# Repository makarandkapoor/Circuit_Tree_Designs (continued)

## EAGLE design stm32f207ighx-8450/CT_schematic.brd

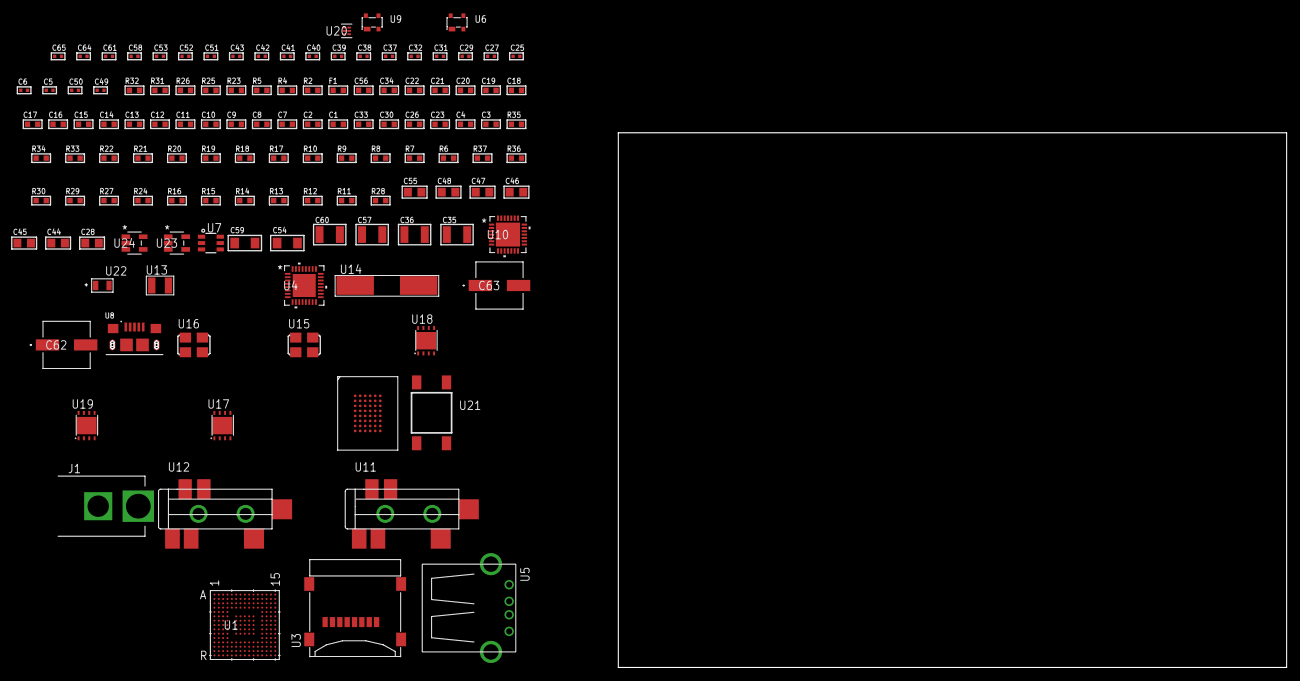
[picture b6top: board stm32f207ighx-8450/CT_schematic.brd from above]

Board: 2 copper layers, 125 parts (0 on the bottom side), 71 nets, no tracks yet.

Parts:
C1: 1e-08; C0603
C2, C7, C56: 1e-06; C0603
C3, C4, C26, C30, C33: 2.2e-06; C0603
C5, C6: 1e-11; C0402
C8, C9, C10, C11, C12, C13, C14, C15, C16, C17, C18, C19, C20, C21, C22: 1e-07; C0603
C23: 4.7e-06; C0603
C25, C27, C29, C31, C32, C39, C40, C41, C42, C43, C61: 1e-07; C0402
C28, C44, C45, C46, C47, C48, C55: 1e-05; C0805
C34: 0.0001; R0603
C35, C36: 2.2e-05; C1210
C37, C38: 1e-09; C0402
C49, C50: 2.2e-11; C0402
C51, C52, C53, C58, C64, C65: 1e-08; C0402
C54, C59: 1e-05; C1206
C57, C60: 1e-05; C1210
C62, C63: 0.0001; EXV-9H
F1: 240.0; L0603
J1: PJ-037B; PJ-037B_PACKAGE
R2, R26, R32: 1000.0; R0603
R4, R5: 4700.0; R0603
R6, R7, R8, R9, R10, R18, R19, R33, R34: 10000.0; R0603
R11, R12, R13, R14, R15, R16, R24, R27, R29, R30: 100000.0; R0603
R17, R20, R21, R22: 47000.0; R0603
R23: 680.0; R0603
R25: 806.0; R0603
R28: 153694.38; R0603
R31: 3900.0; R0603
R35: 82000.0; R0603
R36: 300000.0; R0603
R37: 120000.0; R0603
U1: STM32f207IGH6; UFBGA176_25
U2: IS61WV102416BLL-10MLI
U3: 0472192001; MOLEX_47219-2001
U4: TUSB1210BRHBR; RHB32_3P45X3P45
U5: 61400416021; USB-A-H
U6, U9: prtr5v0u2ax; SOT143B
U7: MAX4995AAUT+T; SOT-23-6
U8: 10118193-0001LF; FCI_10118193-0001LF
U10: WM8731CLSEFL; QFN-28
U11, U12: SJ-43515TS-SMT-TR
U13: ABS07-32.768KHZ-7-T
U14: ABLS-12.288MHZ-B4-T
U15: ASFL1-19.2MHZ-NCS; ASFL1
U16: ASFL1-25MHZ-NCS; ASFL1
U17, U19: LP3878SDX-ADJ/NOPB; WSON-8
U18: LP2951ACSDX/NOPB; WSON-8
U20: TPS3895ADRYR; SON-6
U21: 4-1437565-2; SW_4-1437565-2
U22: Q65110A2395; LGM67K-G1J2-24-Z
U23, U24: nc7sz125m5x; NC7SZ125M5X

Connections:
CLK_CRYSTAL_U1_E1: C5.1, U1.E1, U13.1
CLK_CRYSTAL_U1_F1: C6.1, U1.F1, U13.2
CLK_CRYSTAL_U10_1: C49.1, U10.1, U14.1
CLK_CRYSTAL_U10_2: C50.1, U10.2, U14.2
CLK_U1_G1: U1.G1, U16.3
CLK_U4_1: U4.1, U15.3
GND: C1.2, C2.2, C3.2, C4.2, C5.2, C6.2, C7.2, C8.2, C9.2, C10.2, C11.2, C12.2, C13.2, C14.2, C15.2, C16.2, C17.2, C18.2, C19.2, C20.2, C21.2, C22.2, C23.2, C25.2, C26.2, C27.2, C28.2, C29.2, C30.2, C31.2, C32.2, C33.2, C34.2, C38.2, C39.2, C40.2, C41.2, C42.2, C43.2, C44.2, C45.2, C46.2, C47.2, C48.2, C49.2, C50.2, C51.2, C52.2, C53.2, C54.2, C55.2, C56.2, C57.2, C58.2, C59.2, C60.2, C61.2, C62.2, C63.2, C64.2, C65.2, J1.2, R2.2, R6.2, R7.2, R17.2, R19.2, R20.2, R21.2, R22.2, R26.2, R29.2, R32.2, R35.2, R37.2, U1.D5, U1.D7, U1.D8, U1.D9, U1.F2, U1.F6, U1.F7, U1.F8, U1.F9, U1.F10, U1.F12, U1.G2, U1.G6, U1.G7, U1.G8, U1.G9, U1.G10, U1.G12, U1.H6, U1.H7, U1.H8, U1.H9, U1.H10, U1.H12, U1.J6, U1.J7, U1.J8, U1.J9, U1.J10, U1.K6, U1.K7, U1.K8, U1.K9, U1.K10, U1.M1, U1.M8, U1.M9, U1.N1, U2.D1, U2.E6, U3.6, U3.G1, U3.G2, U3.G3, U3.G4, U4.23, U4.33, U5.4, U5.5, U5.6, U6.1, U7.2, U8.5, U8.6, U8.7, U8.8, U8.9, U9.1, U10.4, U10.15, U10.19, U10.25, U10.26, U10.29, U11.1, U12.1, U15.2, U16.2, U17.3, U17.PAD, U18.3, U18.4, U18.PAD, U19.3, U19.PAD, U20.2, U22.C, U23.1, U23.3, U24.1, U24.3
NET_U1_D6: R6.1, U1.D6
NET_U1_F13: C4.1, U1.F13
NET_U1_J1: R4.1, U1.J1, U23.4
NET_U1_L4: R7.1, U1.L4
NET_U1_M10: C3.1, U1.M10
NET_U1_R1: C1.1, C2.1, F1.1, U1.P1, U1.R1
NET_U1_R15: U21.3, U21.4
NET_U2_A2: R9.1, U2.A2
NET_U2_B5: R8.1, U2.B5
NET_U2_G5: R10.1, U2.G5
NET_U4_11: R18.1, U4.11
NET_U4_12: C33.1, U4.12
NET_U4_14: R19.1, U4.14
NET_U4_20: C30.1, U4.20
NET_U4_27: R5.1, U4.27, U24.4
NET_U5_1: C34.1, U4.22, U5.1, U6.4, U7.1
NET_U5_2: U4.19, U5.2, U6.3
NET_U5_3: U4.18, U5.3, U6.2
NET_U7_3: R17.1, U7.3
NET_U7_4: U4.17, U7.4
NET_U10_20: C43.1, C48.1, U10.20
NET_U11_2: C36.1, R21.1, U11.2
NET_U11_5: C35.1, R20.1, U11.5
NET_U12_5: C37.1, C38.1, R22.1, R23.1, U12.5
NET_U17_1: C53.1, U17.1
NET_U17_6: R25.2, R26.1, U17.6
NET_U17_8: R24.1, U17.8
NET_U18_5: R27.1, U18.5
NET_U18_7: R28.2, R29.1, U18.7
NET_U19_1: C58.1, U19.1
NET_U19_6: R31.2, R32.1, U19.6
NET_U19_8: R30.1, U19.8
NET_U20_1: R34.1, R35.1, U20.1
NET_U20_3: R36.2, R37.1, U20.3
NET_U20_4: R33.1, U20.4, U23.2, U24.2
NET_U21_1: R2.1, U21.1, U21.2
PROC_I2S2_SCK: U1.D14, U10.7
PROC_I2S2_SD: U1.C13, U10.8
PROC_I2S2_WS: U1.B4, U10.9, U10.11
PROC_SDIO_CK: R12.1, U1.A12, U3.5
PROC_SDIO_CMD: R11.1, U1.D12, U3.3
PROC_SDIO_D0: R13.1, U1.G14, U3.7
PROC_SDIO_D1: R14.1, U1.F14, U3.8
PROC_SDIO_D2: R15.1, U1.B14, U3.1
PROC_SDIO_D3: R16.1, U1.B13, U3.2
PROC_USB_OTG_FS_DM: U8.2, U9.3
PROC_USB_OTG_FS_DP: U8.3, U9.2
PROC_USB_OTG_FS_VBUS: U8.1, U9.4
PROC_USB_OTG_HS_ULPI_CK: U1.P4, U4.26
PROC_USB_OTG_HS_ULPI_D0: U1.R2, U4.3
PROC_USB_OTG_HS_ULPI_D1: U1.R5, U4.4
PROC_USB_OTG_HS_ULPI_D2: U1.R4, U4.5
PROC_USB_OTG_HS_ULPI_D3: U1.R12, U4.6
PROC_USB_OTG_HS_ULPI_D4: U1.R13, U4.7
PROC_USB_OTG_HS_ULPI_D5: U1.P12, U4.9
PROC_USB_OTG_HS_ULPI_D6: U1.P13, U4.10
PROC_USB_OTG_HS_ULPI_D7: U1.A6, U4.13
PROC_USB_OTG_HS_ULPI_DIR: U1.E4, U4.31
PROC_USB_OTG_HS_ULPI_NXT: U1.H4, U4.2
PROC_USB_OTG_HS_ULPI_STP: U1.M2, U4.29
VCC_S1_8V6: C54.1, C56.1, C59.1, C62.1, C63.1, J1.1, R24.2, R30.2, U17.4, U18.8, U19.4
VCC_TIER1_1V8: C7.1, C8.1, C9.1, C10.1, C11.1, C12.1, C13.1, C14.1, C15.1, C16.1, C17.1, C18.1, C19.1, C20.1, C21.1, C22.1, C23.1, C27.1, C28.1, C31.1, C32.1, C39.1, C40.1, C41.1, C42.1, C44.1, C45.1, C46.1, C47.1, C55.1, C61.1, C64.1, C65.1, F1.2, R4.2, R5.2, R11.2, R12.2, R13.2, R14.2, R15.2, R16.2, R18.2, R25.1, R33.2, R34.2, R36.1, U1.C1, U1.C5, U1.C7, U1.C8, U1.C9, U1.F3, U1.G3, U1.G13, U1.H13, U1.J12, U1.J13, U1.K4, U1.N8, U1.N9, U1.N10, U3.4, U4.28, U4.30, U4.32, U10.3, U10.5, U10.12, U10.18, U17.5, U20.6, U23.5, U24.5
VCC_TIER1_3V3: C25.1, C26.1, C29.1, C51.1, C52.1, C57.1, R8.2, R9.2, R10.2, R27.2, R28.1, U2.D6, U2.E1, U4.21, U15.4, U16.4, U18.1
VCC_TIER1_5V0: C60.1, R31.1, U7.5, U19.5

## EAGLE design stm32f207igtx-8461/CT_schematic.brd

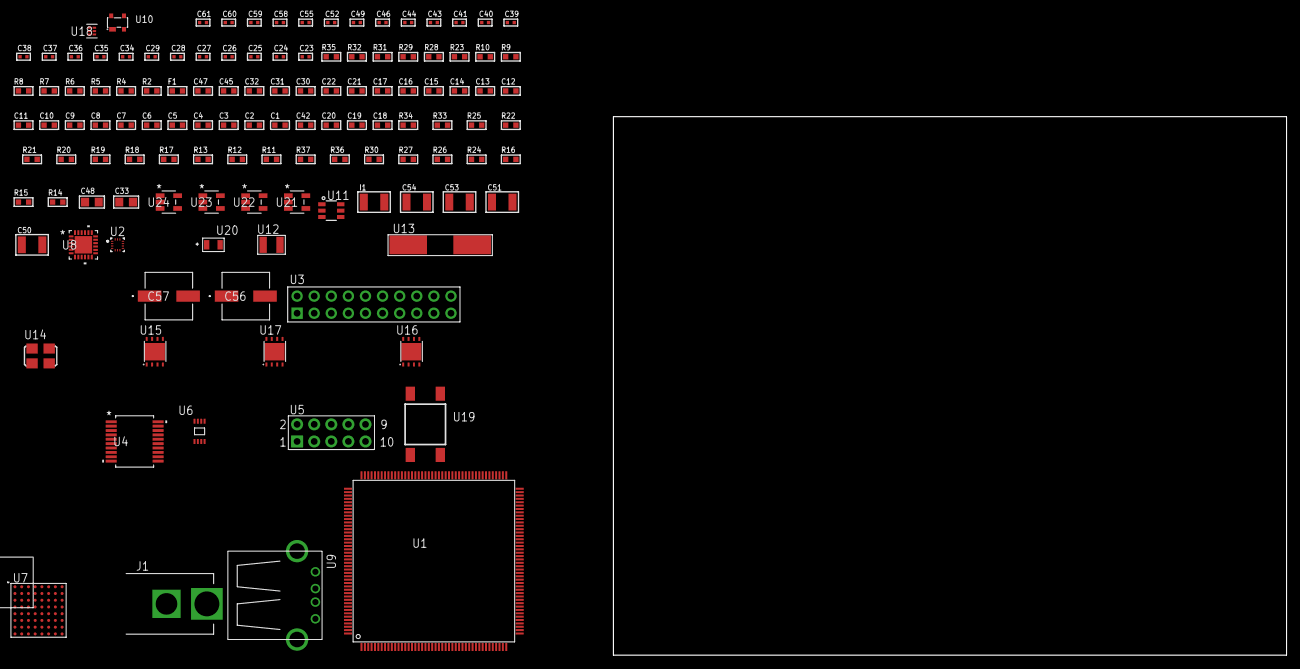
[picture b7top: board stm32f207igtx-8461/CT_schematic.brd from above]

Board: 2 copper layers, 100.0 x 80.0 mm, 123 parts (0 on the bottom side), 120 nets, no tracks yet.

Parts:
C1, C22, C30, C31, C32: 1e-06; C0603
C2, C3, C4, C5, C6, C7, C8, C9, C10, C11, C12, C13, C14, C15, C16, C17: 1e-07; C0603
C18: 4.7e-06; C0603
C19, C20, C42: 2.2e-06; C0603
C21: 1e-08; C0603
C23, C24, C25, C26: 1e-11; C0402
C27, C28, C29, C35, C37, C39, C55: 1e-07; C0402
C33: 4.7e-06; C0805
C34, C36, C38, C40, C41, C43, C44, C46, C49, C52, C58, C59, C60, C61: 1e-08; C0402
C45: 0.0001; R0603
C47: 8e-07; R0603
C48: 1e-05; C0805
C50, C51, C53, C54: 1e-05; C1210
C56, C57: 0.0001; EXV-9H
F1: 240.0; L0603
I1: 1.5e-05; L1210
J1: PJ-037B; PJ-037B_PACKAGE
R2, R29, R32: 1000.0; R0603
R4, R5, R6: 4700.0; R0603
R7, R8, R9, R10: 2200.0; R0603
R11, R12, R13, R17, R18, R19, R20, R21, R33, R34: 10000.0; R0603
R14, R15, R16, R24, R26, R27, R30: 100000.0; R0603
R22: 47000.0; R0603
R23: 8060.0; R0603
R25: 36000.0; R0603
R28: 2231.0; R0603
R31: 3900.0; R0603
R35: 9100.0; R0603
R36: 680000.0; R0603
R37: 120000.0; R0603
U1: STM32F207IGT6; LQFP176
U2: BMC150; LGA14R35P5X6_200X200X100
U3: TST-110-05-T-D-RA
U4: MAX3218EAP+T; SSOP-20
U5: HTSS-105-01-G-D
U6: 24AA00T-I/MNY; TDFN-8/6MM
U7: PC28F512P33BFD
U8: USB3317C-CP-TR; QFN-24
U9: 61400416021; USB-A-H
U10: prtr5v0u2ax; SOT143B
U11: MAX4995AAUT+T; SOT-23-6
U12: ABS07-32.768KHZ-7-T
U13: ABLS-25.000MHZ-B2F-T
U14: ASFL1-26MHZ-NCS; ASFL1
U15: LP2951ACSDX/NOPB; WSON-8
U16, U17: LP3878SDX-ADJ/NOPB; WSON-8
U18: TPS3895ADRYR; SON-6
U19: 4-1437565-2; SW_4-1437565-2
U20: Q65110A2395; LGM67K-G1J2-24-Z
U21, U22, U23, U24: nc7sz125m5x; NC7SZ125M5X

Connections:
CLK_CRYSTAL_U1_9: C23.1, U1.9, U12.1
CLK_CRYSTAL_U1_10: C24.1, U1.10, U12.2
CLK_CRYSTAL_U1_29: C25.1, U1.29, U13.1
CLK_CRYSTAL_U1_30: C26.1, U1.30, U13.2
CLK_U8_23: U8.23, U14.3
GND: C1.2, C2.2, C3.2, C4.2, C5.2, C6.2, C7.2, C8.2, C9.2, C10.2, C11.2, C12.2, C13.2, C14.2, C15.2, C16.2, C17.2, C18.2, C19.2, C20.2, C21.2, C22.2, C23.2, C24.2, C25.2, C26.2, C27.2, C28.2, C29.2, C30.2, C31.2, C32.2, C34.2, C35.2, C36.2, C37.2, C38.2, C39.2, C40.2, C41.2, C42.2, C43.2, C44.2, C45.2, C46.2, C47.2, C48.2, C49.2, C50.2, C51.2, C52.2, C53.2, C54.2, C55.2, C56.2, C57.2, C58.2, C59.2, C60.2, C61.2, J1.2, R2.2, R11.2, R22.2, R23.2, R26.2, R29.2, R32.2, R35.2, R37.2, U1.14, U1.22, U1.37, U1.48, U1.61, U1.71, U1.90, U1.102, U1.113, U1.126, U1.135, U1.148, U1.158, U2.1, U2.6, U2.7, U2.9, U3.4, U3.6, U3.8, U3.10, U3.12, U3.14, U3.16, U3.18, U3.20, U4.5, U4.17, U4.20, U5.9, U6.4, U7.B2, U7.H2, U7.H4, U7.H6, U8.1, U8.25, U9.4, U9.5, U9.6, U10.1, U11.2, U14.2, U15.3, U15.4, U15.PAD, U16.3, U16.PAD, U17.3, U17.PAD, U18.2, U20.C, U21.2, U21.3, U22.1, U22.3, U23.1, U23.3, U24.1, U24.3
NET_U1_31: R5.1, U1.31, U23.4
NET_U1_39: C21.1, C22.1, F1.1, U1.38, U1.39
NET_U1_45: R9.1, U1.45, U6.6
NET_U1_46: R10.1, U1.46, U6.5
NET_U1_81: C19.1, U1.81
NET_U1_125: C20.1, U1.125
NET_U1_164: R7.1, U1.164, U2.11
NET_U1_166: R11.1, U1.166
NET_U1_168: R8.1, U1.168, U2.14
NET_U1_176: U19.3, U19.4
NET_U4_1: I1.1, U4.1
NET_U4_2: R14.1, U4.2
NET_U4_3: R15.1, U4.3
NET_U4_4: R16.1, U4.4
NET_U4_15: C32.1, U4.15
NET_U4_16: C33.2, U4.16
NET_U4_18: C33.1, U4.18
NET_U4_19: C31.1, U4.19
NET_U5_3: U4.12, U5.3
NET_U5_4: U4.11, U5.4
NET_U5_5: U4.14, U5.5
NET_U5_6: U4.13, U5.6
NET_U7_A4: C39.1, C40.1, U7.A4
NET_U7_C6: R20.1, U7.C6
NET_U7_D4: R4.1, U7.D4, U22.4
NET_U8_4: C42.1, U8.4
NET_U8_22: R6.1, U8.22, U24.4
NET_U8_24: R23.1, U8.24
NET_U9_1: C45.1, U8.2, U9.1, U10.4, U11.1
NET_U9_2: U8.5, U9.2, U10.3
NET_U9_3: U8.6, U9.3, U10.2
NET_U11_3: R22.1, U11.3
NET_U11_4: U8.7, U11.4
NET_U15_5: R24.1, U15.5
NET_U15_7: R25.2, R26.1, U15.7
NET_U16_1: C49.1, U16.1
NET_U16_6: R28.2, R29.1, U16.6
NET_U16_8: R27.1, U16.8
NET_U17_1: C52.1, U17.1
NET_U17_6: R31.2, R32.1, U17.6
NET_U17_8: R30.1, U17.8
NET_U18_1: R34.1, R35.1, U18.1
NET_U18_3: R36.2, R37.1, U18.3
NET_U18_4: R33.1, U18.4, U21.4, U22.2, U23.2, U24.2
NET_U19_1: R2.1, U19.1, U19.2
PROC_FSMC_A0: U1.16, U7.A1
PROC_FSMC_A1: U1.17, U7.B1
PROC_FSMC_A2: U1.18, U7.C1
PROC_FSMC_A3: U1.19, U7.D1
PROC_FSMC_A4: U1.20, U7.D2
PROC_FSMC_A5: U1.21, U7.A2
PROC_FSMC_A6: U1.60, U7.C2
PROC_FSMC_A7: U1.63, U7.A3
PROC_FSMC_A8: U1.64, U7.B3
PROC_FSMC_A9: U1.65, U7.C3
PROC_FSMC_A10: U1.66, U7.D3
PROC_FSMC_A11: U1.67, U7.C4
PROC_FSMC_A12: U1.106, U7.A5
PROC_FSMC_A13: U1.107, U7.B5
PROC_FSMC_A14: U1.108, U7.C5
PROC_FSMC_A15: U1.109, U7.D7
PROC_FSMC_A16: U1.99, U7.D8
PROC_FSMC_A17: U1.100, U7.A7
PROC_FSMC_A18: U1.101, U7.B7
PROC_FSMC_A19: U1.2, U7.C7
PROC_FSMC_A20: U1.3, U7.C8
PROC_FSMC_A21: U1.4, U7.A8
PROC_FSMC_A22: U1.5, U7.G1
PROC_FSMC_A23: U1.1, U7.H8
PROC_FSMC_A24: U1.156, U7.B6
PROC_FSMC_CLK: U1.145, U7.E6
PROC_FSMC_D0: U1.104, U7.F2
PROC_FSMC_D1: U1.105, U7.E2
PROC_FSMC_D2: U1.142, U7.G3
PROC_FSMC_D3: U1.143, U7.E4
PROC_FSMC_D4: U1.68, U7.E5
PROC_FSMC_D5: U1.69, U7.G5
PROC_FSMC_D6: U1.70, U7.G6
PROC_FSMC_D7: U1.73, U7.H7
PROC_FSMC_D8: U1.74, U7.E1
PROC_FSMC_D9: U1.75, U7.E3
PROC_FSMC_D10: U1.76, U7.F3
PROC_FSMC_D11: U1.77, U7.F4
PROC_FSMC_D12: U1.78, U7.F5
PROC_FSMC_D13: U1.96, U7.H5
PROC_FSMC_D14: U1.97, U7.G7
PROC_FSMC_D15: U1.98, U7.E7
PROC_FSMC_NE4: R18.1, U1.155, U7.B4
PROC_FSMC_NL: R17.1, U1.165, U7.F6
PROC_FSMC_NOE: R19.1, U1.146, U7.F8
PROC_FSMC_NWAIT: U1.150, U7.F7
PROC_FSMC_NWE: R21.1, U1.147, U7.G8
PROC_SYS_JTCK_SWCLK: U1.137, U3.9
PROC_SYS_JTDO_SWO: U1.161, U3.13
PROC_SYS_JTMS_SWDIO: U1.124, U3.7
PROC_UART4_RX: U1.41, U4.9
PROC_UART4_TX: U1.40, U4.7
PROC_USB_OTG_HS_ULPI_CK: U1.51, U8.12
PROC_USB_OTG_HS_ULPI_D0: U1.47, U8.16
PROC_USB_OTG_HS_ULPI_D1: U1.56, U8.15
PROC_USB_OTG_HS_ULPI_D2: U1.57, U8.14
PROC_USB_OTG_HS_ULPI_D3: U1.79, U8.13
PROC_USB_OTG_HS_ULPI_D4: U1.80, U8.11
PROC_USB_OTG_HS_ULPI_D5: U1.92, U8.10
PROC_USB_OTG_HS_ULPI_D6: U1.93, U8.9
PROC_USB_OTG_HS_ULPI_D7: U1.163, U8.8
PROC_USB_OTG_HS_ULPI_DIR: U1.13, U8.19
PROC_USB_OTG_HS_ULPI_NXT: U1.35, U8.18
PROC_USB_OTG_HS_ULPI_STP: U1.32, U8.20
RST_OUT_U3_SRESET_B: R13.1, U3.15, U21.1
VCC_S1_13V0: C47.1, C50.1, C53.1, C56.1, C57.1, J1.1, R27.2, R30.2, U15.8, U16.4, U17.4
VCC_TIER1_1V8: C27.1, C44.1, C48.1, C58.1, C59.1, C60.1, C61.1, R24.2, R25.1, U2.8, U8.21, U15.1, U21.5, U22.5, U23.5, U24.5
VCC_TIER1_3V3: C1.1, C2.1, C3.1, C4.1, C5.1, C6.1, C7.1, C8.1, C9.1, C10.1, C11.1, C12.1, C13.1, C14.1, C15.1, C16.1, C17.1, C18.1, C28.1, C29.1, C30.1, C34.1, C35.1, C36.1, C37.1, C38.1, C41.1, C43.1, C46.1, C51.1, C55.1, F1.2, I1.2, R4.2, R5.2, R6.2, R7.2, R8.2, R9.2, R10.2, R12.1, R12.2, R13.2, R14.2, R15.2, R16.2, R17.2, R18.2, R19.2, R20.2, R21.2, R28.1, R33.2, R34.2, R36.1, U1.6, U1.15, U1.23, U1.36, U1.49, U1.62, U1.72, U1.82, U1.91, U1.103, U1.114, U1.127, U1.136, U1.149, U1.159, U1.172, U2.10, U2.12, U2.13, U3.1, U4.6, U6.8, U7.A6, U7.D5, U7.D6, U7.G4, U7.H3, U8.3, U8.17, U14.4, U16.5, U18.6
VCC_TIER1_5V0: C54.1, R31.1, U11.5, U17.5

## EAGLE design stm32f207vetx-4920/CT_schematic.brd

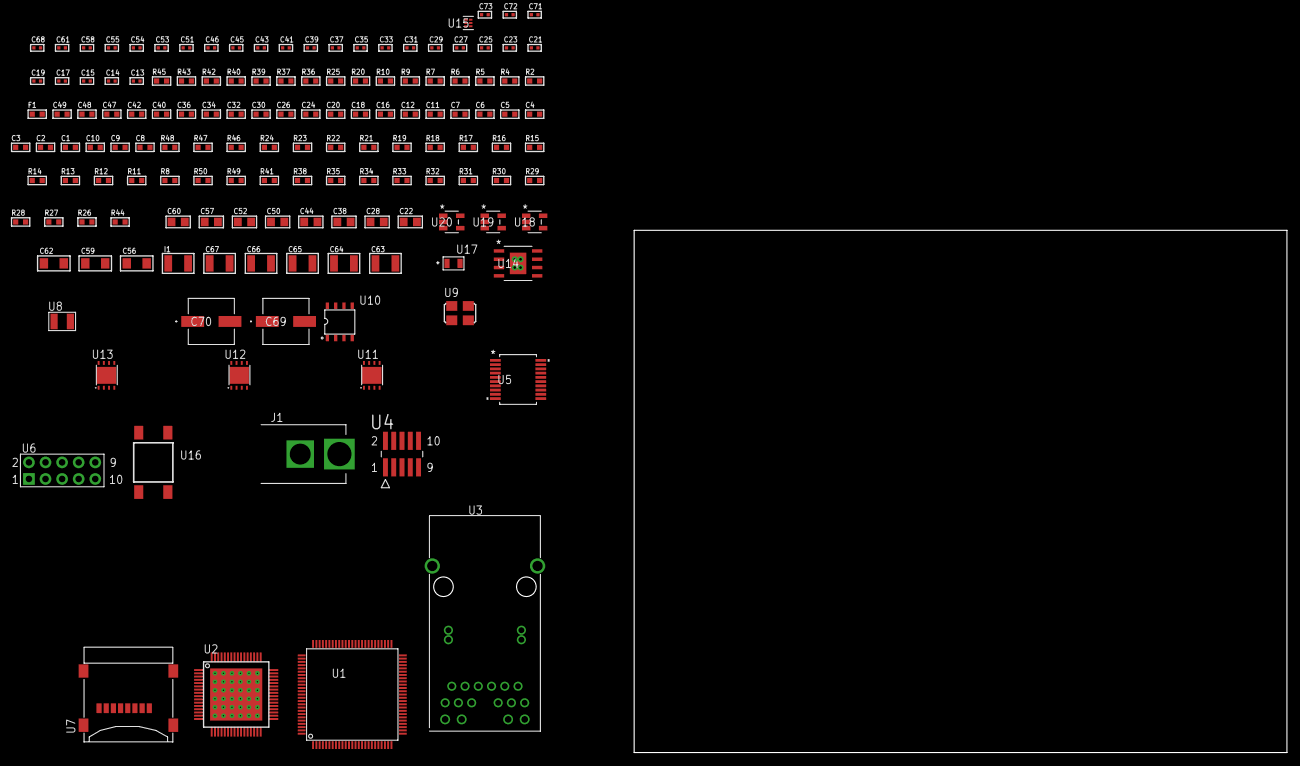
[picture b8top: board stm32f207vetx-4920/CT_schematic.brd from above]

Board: 2 copper layers, 100.0 x 80.0 mm, 144 parts (0 on the bottom side), 97 nets, no tracks yet.

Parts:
C1, C12, C16, C18, C20, C24, C26, C30, C32, C34, C36, C40, C42, C47, C48, C49: 1e-06; C0603
C2, C3, C4, C5, C6, C7: 1e-07; C0603
C8: 4.7e-06; C0603
C9, C10: 2.2e-06; C0603
C11: 1e-08; C0603
C13, C14: 1e-11; C0402
C15, C17, C19, C21, C25, C27, C31, C33, C35, C37, C41, C43, C46, C51, C68: 1e-07; C0402
C22, C28, C38, C44, C52, C57, C60: 1e-05; C0805
C23, C29, C39, C45, C53, C54, C55, C58, C61, C71, C72, C73: 1e-08; C0402
C50: 4.7e-06; C0805
C56, C59, C62: 1e-05; C1206
C63, C64, C65, C66, C67: 1e-05; C1210
C69, C70: 0.0001; EXV-9H
F1: 240.0; L0603
I1: 1.5e-05; L1210
J1: PJ-037B; PJ-037B_PACKAGE
R2, R37, R40, R43: 1000.0; R0603
R4, R5: 4700.0; R0603
R6, R7, R45: 2200.0; R0603
R8, R11, R13, R14, R15, R16, R17, R18, R19, R21, R22, R23, R24, R46, R47: 10000.0; R0603
R9, R10: 200.0; R0603
R12: 11000.0; R0603
R20: 2490.0; R0603
R25: 5.0; R0603
R26, R27, R28, R29, R30, R31, R32, R33, R34, R35, R38, R41: 100000.0; R0603
R36: 100.0; R0603
R39: 806.0; R0603
R42: 1500.0; R0603
R44: 4031.5447154472; R0603
R48: 82000.0; R0603
R49: 300000.0; R0603
R50: 120000.0; R0603
U1: STM32F207VET6; LQFP100
U2: DP83867IRPAPT; HTQFP-64-EXP
U3: 7499511611A
U4: FTSH-105-01-L-DV-K; SAMTEC_FTSH-105-01-L-DV-K
U5: MAX3218EAP+T; SSOP-20
U6: HTSS-105-01-G-D
U7: 0472192001; MOLEX_47219-2001
U8: ABS07-32.768KHZ-7-T
U9: ASFL1-25MHZ-NCS; ASFL1
U10: idt74fct38072; IDT74FCT38072
U11, U12, U13: LP3878SDX-ADJ/NOPB; WSON-8
U14: MIC5234YME; SOIC-8_EP
U15: TPS3895ADRYR; SON-6
U16: 4-1437565-2; SW_4-1437565-2
U17: Q65110A2395; LGM67K-G1J2-24-Z
U18, U19, U20: nc7sz125m5x; NC7SZ125M5X

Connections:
CLK_CRYSTAL_U1_8: C13.1, U1.8, U8.1
CLK_CRYSTAL_U1_9: C14.1, U1.9, U8.2
CLK_U1_12: U1.12, U10.7
CLK_U2_19: U2.19, U10.6
CLK_U10_3: U9.3, U10.3
GND: C1.2, C2.2, C3.2, C4.2, C5.2, C6.2, C7.2, C8.2, C9.2, C10.2, C11.2, C12.2, C13.2, C14.2, C15.2, C16.2, C17.2, C18.2, C19.2, C20.2, C21.2, C22.2, C23.2, C24.2, C25.2, C26.2, C27.2, C28.2, C29.2, C30.2, C31.2, C32.2, C33.2, C34.2, C35.2, C36.2, C37.2, C38.2, C39.2, C40.2, C41.2, C42.2, C43.2, C44.2, C45.2, C46.2, C47.2, C48.2, C49.2, C51.2, C52.2, C53.2, C54.2, C55.2, C56.2, C57.2, C58.2, C59.2, C60.2, C61.2, C62.2, C63.2, C64.2, C65.2, C66.2, C67.2, C68.2, C69.2, C70.2, C71.2, C72.2, C73.2, J1.2, R2.2, R8.2, R12.2, R13.2, R14.2, R15.2, R16.2, R17.2, R18.2, R19.2, R24.2, R25.2, R37.2, R40.2, R43.2, R45.2, R48.2, R50.2, U1.10, U1.20, U1.27, U1.74, U2.EXP, U3.17, U3.20, U3.Z1, U3.Z2, U4.3, U4.5, U5.5, U5.17, U5.20, U6.9, U7.6, U7.G1, U7.G2, U7.G3, U7.G4, U9.2, U10.4, U10.5, U10.8, U11.3, U11.PAD, U12.3, U12.PAD, U13.3, U13.PAD, U14.7, U14.EPAD, U15.2, U17.C, U18.2, U18.3, U19.1, U19.3, U20.1, U20.3
NET_U1_14: R5.1, U1.14, U20.4
NET_U1_16: R6.1, U1.16, U2.20
NET_U1_22: C11.1, C12.1, F1.1, U1.21, U1.22
NET_U1_25: R7.1, U1.25, U2.21
NET_U1_49: C9.1, U1.49
NET_U1_73: C10.1, U1.73
NET_U1_94: R8.1, U1.94
NET_U1_98: U16.3, U16.4
NET_U2_15: R12.1, U2.15
NET_U2_24: R18.1, U2.24
NET_U2_25: R19.1, U2.25
NET_U2_31: R14.1, U2.31
NET_U2_32: R15.1, U2.32
NET_U2_33: R16.1, U2.33
NET_U2_34: R17.1, U2.34
NET_U2_40: R13.1, U2.40
NET_U2_59: R4.1, U2.59, U19.4
NET_U2_60: R11.1, U2.60
NET_U3_2: U2.11, U3.2
NET_U3_3: U2.10, U3.3
NET_U3_4: U2.5, U3.4
NET_U3_5: U2.6, U3.5
NET_U3_6: C15.1, U3.1, U3.6, U3.7, U3.12
NET_U3_8: U2.13, U3.8
NET_U3_9: U2.14, U3.9
NET_U3_10: U2.3, U3.10
NET_U3_11: U2.2, U3.11
NET_U3_18: R9.1, U3.18
NET_U3_19: R10.1, U3.19
NET_U4_9: R25.1, U4.9
NET_U5_1: I1.1, U5.1
NET_U5_2: R26.1, U5.2
NET_U5_3: R27.1, U5.3
NET_U5_4: R28.1, U5.4
NET_U5_15: C49.1, U5.15
NET_U5_16: C50.2, U5.16
NET_U5_18: C50.1, U5.18
NET_U5_19: C48.1, U5.19
NET_U6_3: U5.12, U6.3
NET_U6_4: U5.11, U6.4
NET_U6_5: U5.14, U6.5
NET_U6_6: U5.13, U6.6
NET_U11_1: C55.1, U11.1
NET_U11_6: R36.2, R37.1, U11.6
NET_U11_8: R35.1, U11.8
NET_U12_1: C58.1, U12.1
NET_U12_6: R39.2, R40.1, U12.6
NET_U12_8: R38.1, U12.8
NET_U13_1: C61.1, U13.1
NET_U13_6: R42.2, R43.1, U13.6
NET_U13_8: R41.1, U13.8
NET_U14_4: R44.2, R45.1, U14.4
NET_U15_1: R47.1, R48.1, U15.1
NET_U15_3: R49.2, R50.1, U15.3
NET_U15_4: R46.1, U15.4, U18.4, U19.2, U20.2
NET_U16_1: R2.1, U16.1, U16.2
PROC_ETH_COL: U1.26, U2.55
PROC_ETH_CRS: U1.23, U2.56
PROC_ETH_RXD0: R20.1, U1.33, U2.44
PROC_ETH_RXD1: U1.34, U2.45
PROC_ETH_RXD2: U1.35, U2.46
PROC_ETH_RXD3: U1.36, U2.47
PROC_ETH_RX_CLK: U1.24, U2.43
PROC_ETH_RX_DV: U1.32, U2.53
PROC_ETH_RX_ER: U1.47, U2.54
PROC_ETH_TXD0: U1.51, U2.38
PROC_ETH_TXD1: U1.52, U2.37
PROC_ETH_TXD2: U1.17, U2.36
PROC_ETH_TXD3: U1.1, U2.35
PROC_ETH_TX_CLK: U1.18, U2.30
PROC_ETH_TX_EN: U1.48, U2.52
PROC_SDIO_CK: R30.1, U1.80, U7.5
PROC_SDIO_CMD: R29.1, U1.83, U7.3
PROC_SDIO_D0: R31.1, U1.65, U7.7
PROC_SDIO_D1: R32.1, U1.66, U7.8
PROC_SDIO_D2: R33.1, U1.78, U7.1
PROC_SDIO_D3: R34.1, U1.79, U7.2
PROC_SYS_JTDI: R22.1, U1.77, U4.8
PROC_SYS_JTDO_SWO: U1.89, U4.6
PROC_SYS_JTMS_SWDIO: R23.1, U1.72, U4.2
PROC_SYS_TRACECLK: R24.1, U1.76, U4.4
PROC_USART1_CTS: U1.70, U5.8
PROC_USART1_RTS: U1.71, U5.10
PROC_USART1_RX: U1.69, U5.9
PROC_USART1_TX: U1.68, U5.7
RST_OUT_U4_JTAG_RST_B: R21.1, U4.10, U18.1
VCC_S1_8V6: C56.1, C59.1, C62.1, C64.1, C65.1, C69.1, C70.1, J1.1, R35.2, R38.2, R41.2, U11.4, U12.4, U13.4, U14.5, U14.8
VCC_TIER1_1V1: C30.1, C31.1, C32.1, C33.1, C34.1, C35.1, C36.1, C37.1, C38.1, C39.1, C57.1, R36.1, U2.8, U2.29, U2.42, U2.58, U11.5
VCC_TIER1_1V8: C1.1, C2.1, C3.1, C4.1, C5.1, C6.1, C7.1, C8.1, C16.1, C17.1, C18.1, C19.1, C20.1, C21.1, C22.1, C23.1, C40.1, C41.1, C42.1, C43.1, C44.1, C45.1, C46.1, C47.1, C51.1, C52.1, C60.1, C68.1, C71.1, C72.1, C73.1, F1.2, I1.2, R4.2, R5.2, R6.2, R7.2, R11.2, R20.2, R21.2, R22.2, R23.2, R26.2, R27.2, R28.2, R29.2, R30.2, R31.2, R32.2, R33.2, R34.2, R39.1, R46.2, R47.2, R49.1, U1.6, U1.11, U1.19, U1.28, U1.50, U1.75, U1.100, U2.17, U2.23, U2.41, U2.57, U2.64, U4.1, U5.6, U7.4, U12.5, U15.6, U18.5, U19.5, U20.5
VCC_TIER1_2V5: C24.1, C25.1, C26.1, C27.1, C28.1, C29.1, C63.1, R42.1, U2.4, U2.12, U13.5
VCC_TIER1_3V3: C53.1, C54.1, C66.1, C67.1, R44.1, U9.4, U10.1, U10.2, U14.1
